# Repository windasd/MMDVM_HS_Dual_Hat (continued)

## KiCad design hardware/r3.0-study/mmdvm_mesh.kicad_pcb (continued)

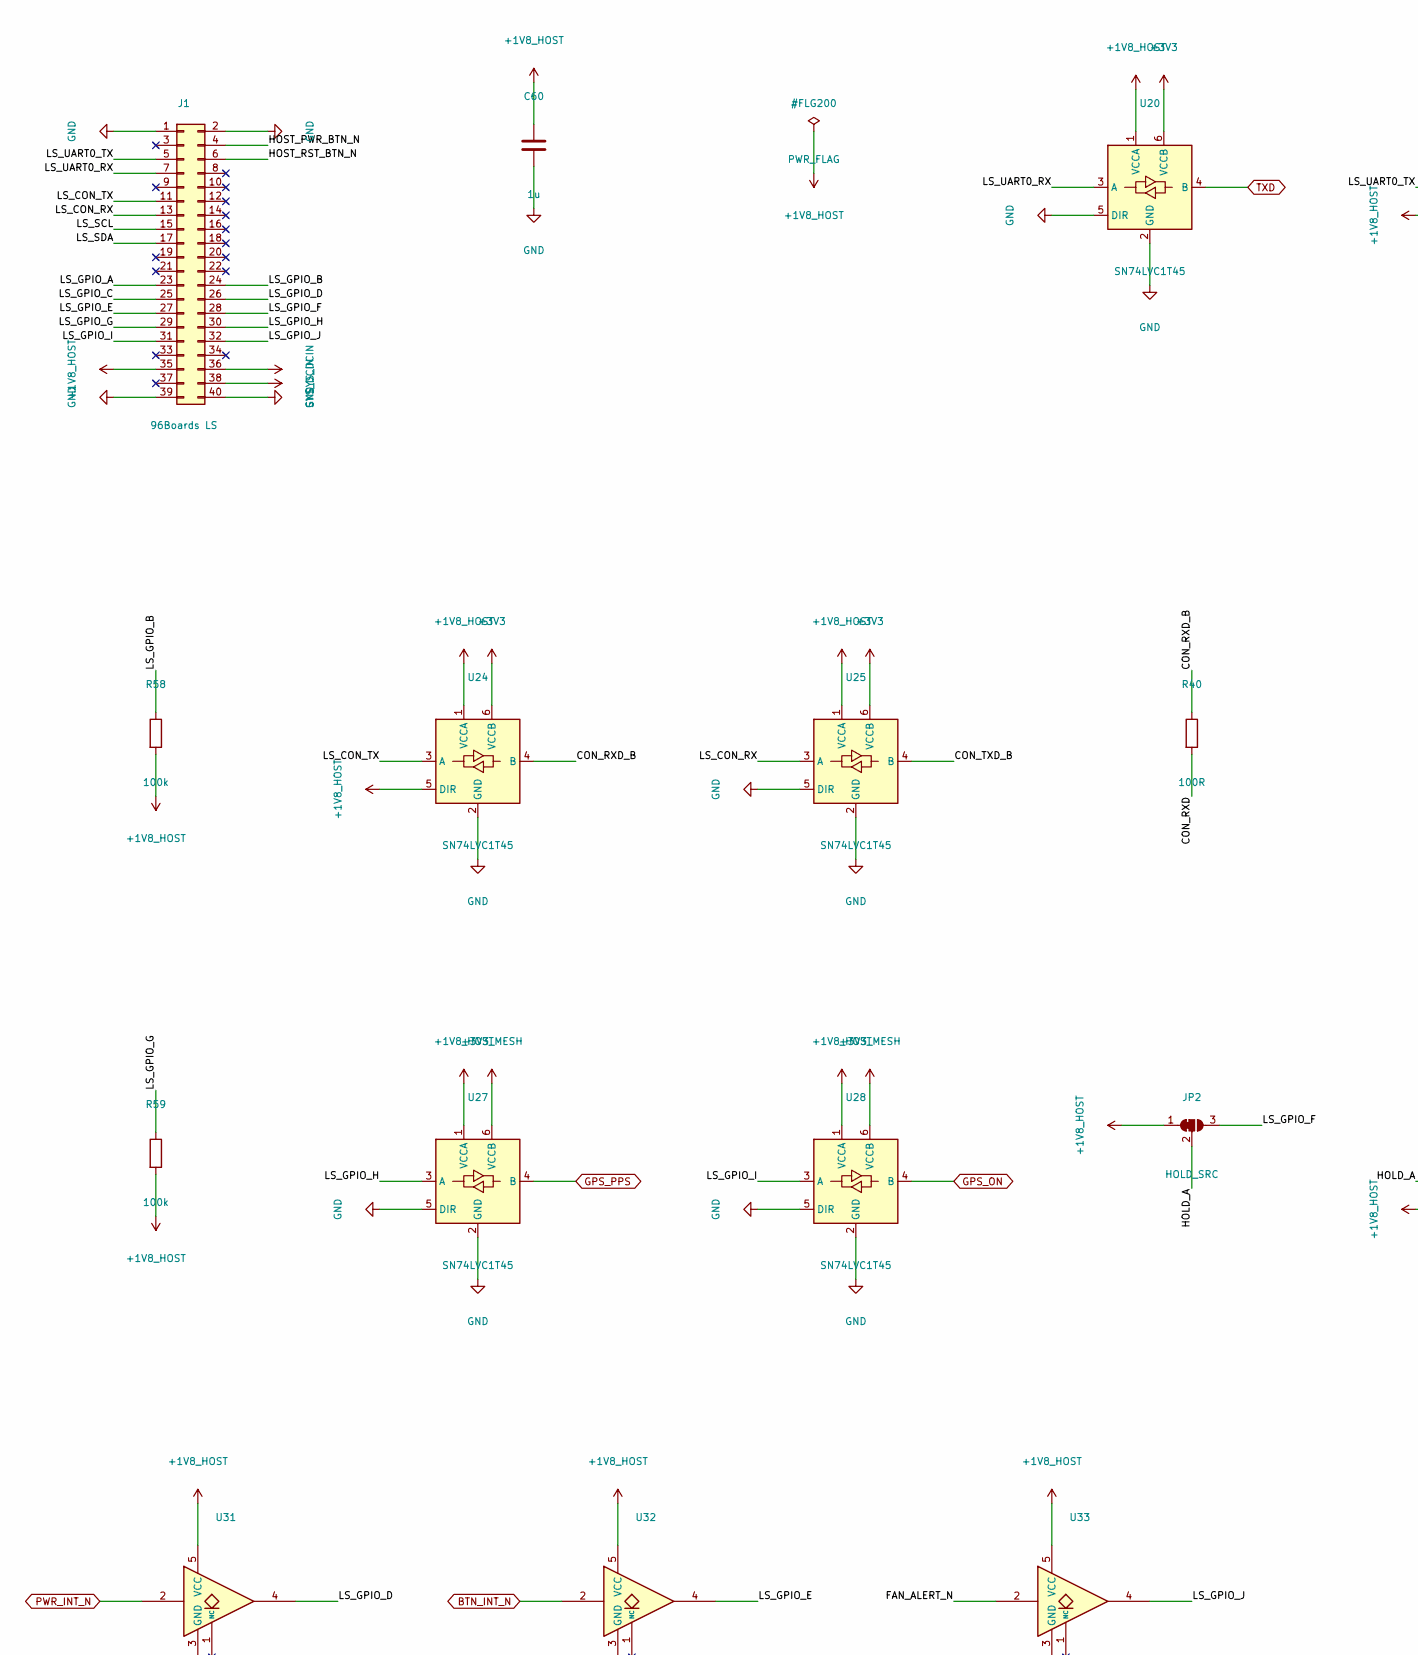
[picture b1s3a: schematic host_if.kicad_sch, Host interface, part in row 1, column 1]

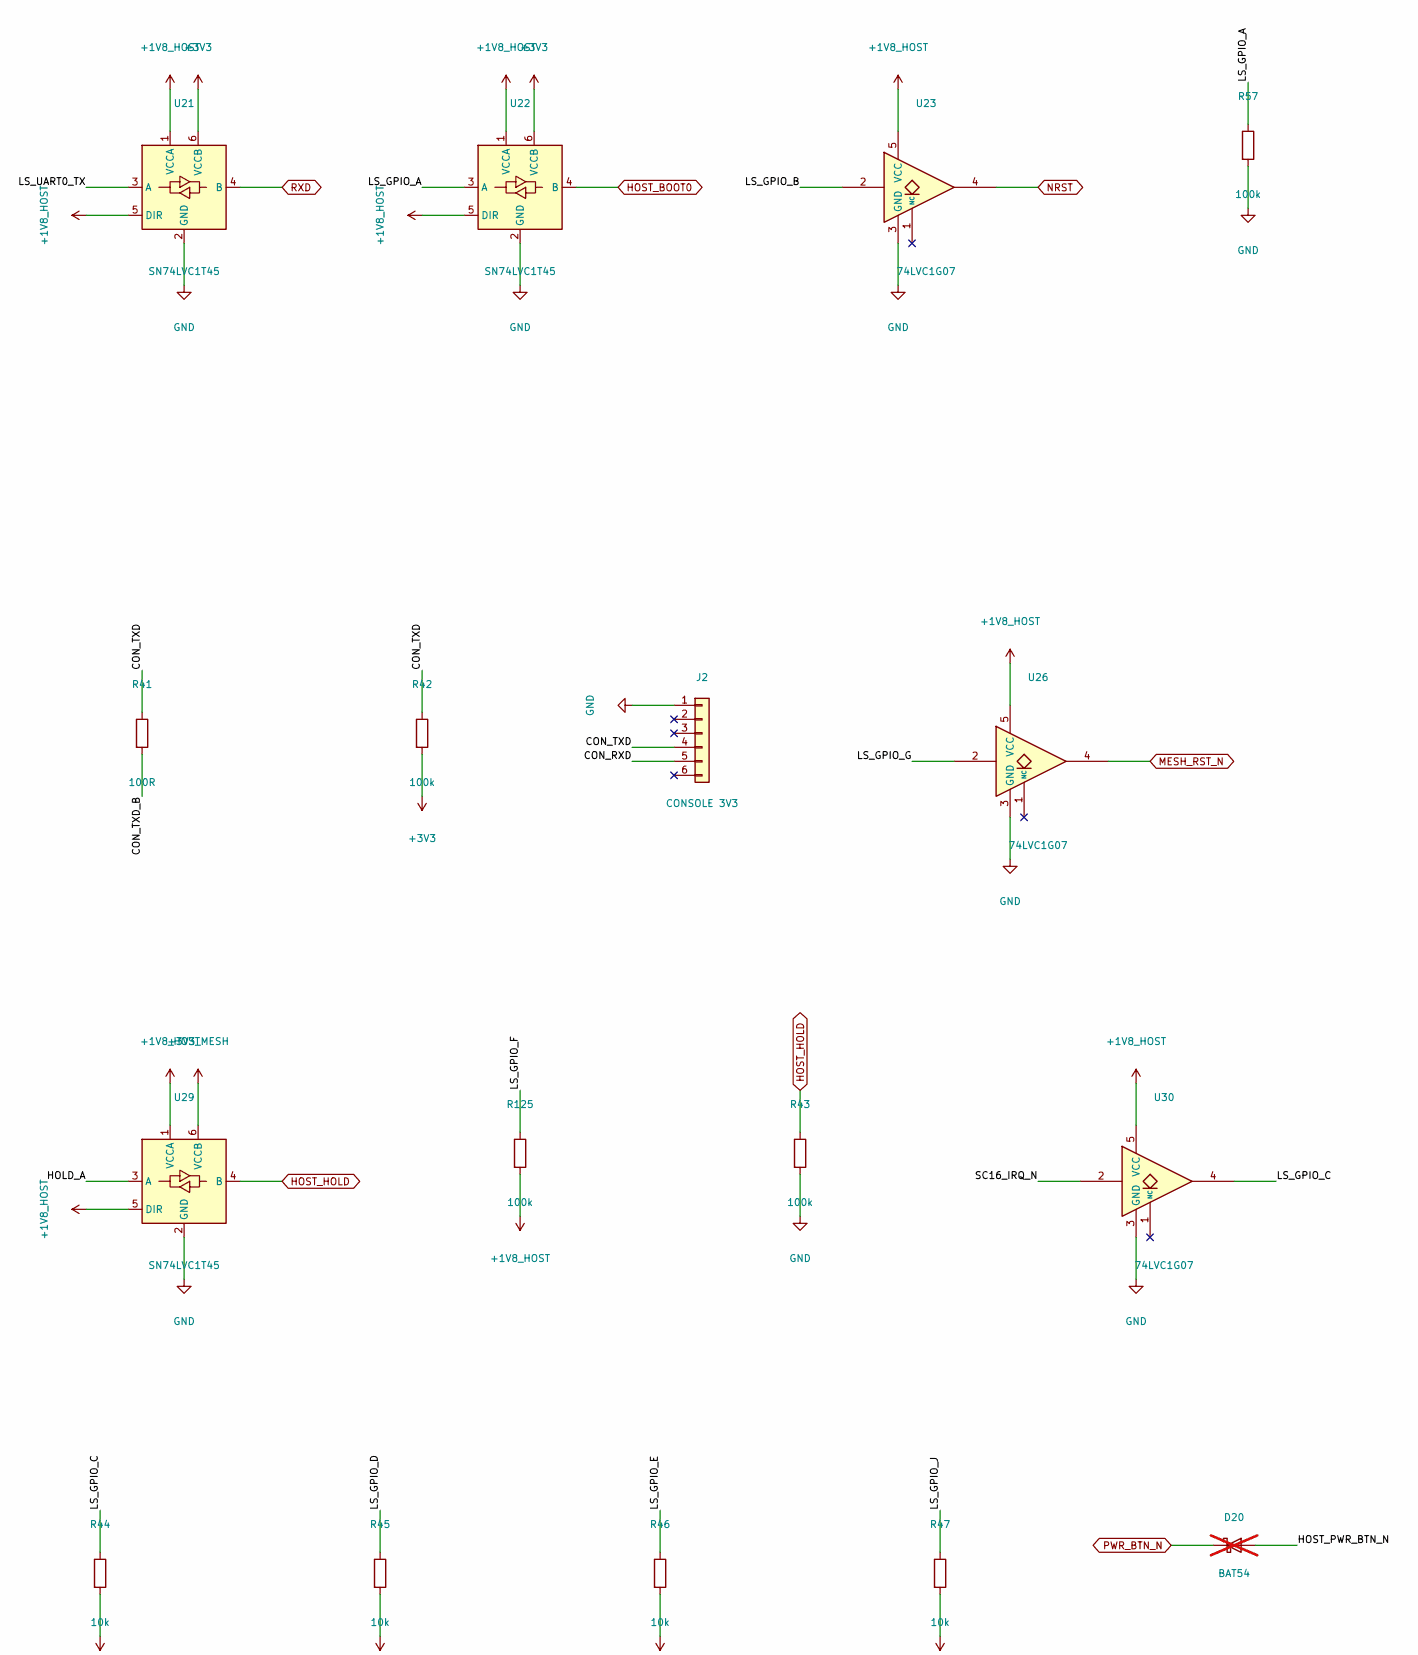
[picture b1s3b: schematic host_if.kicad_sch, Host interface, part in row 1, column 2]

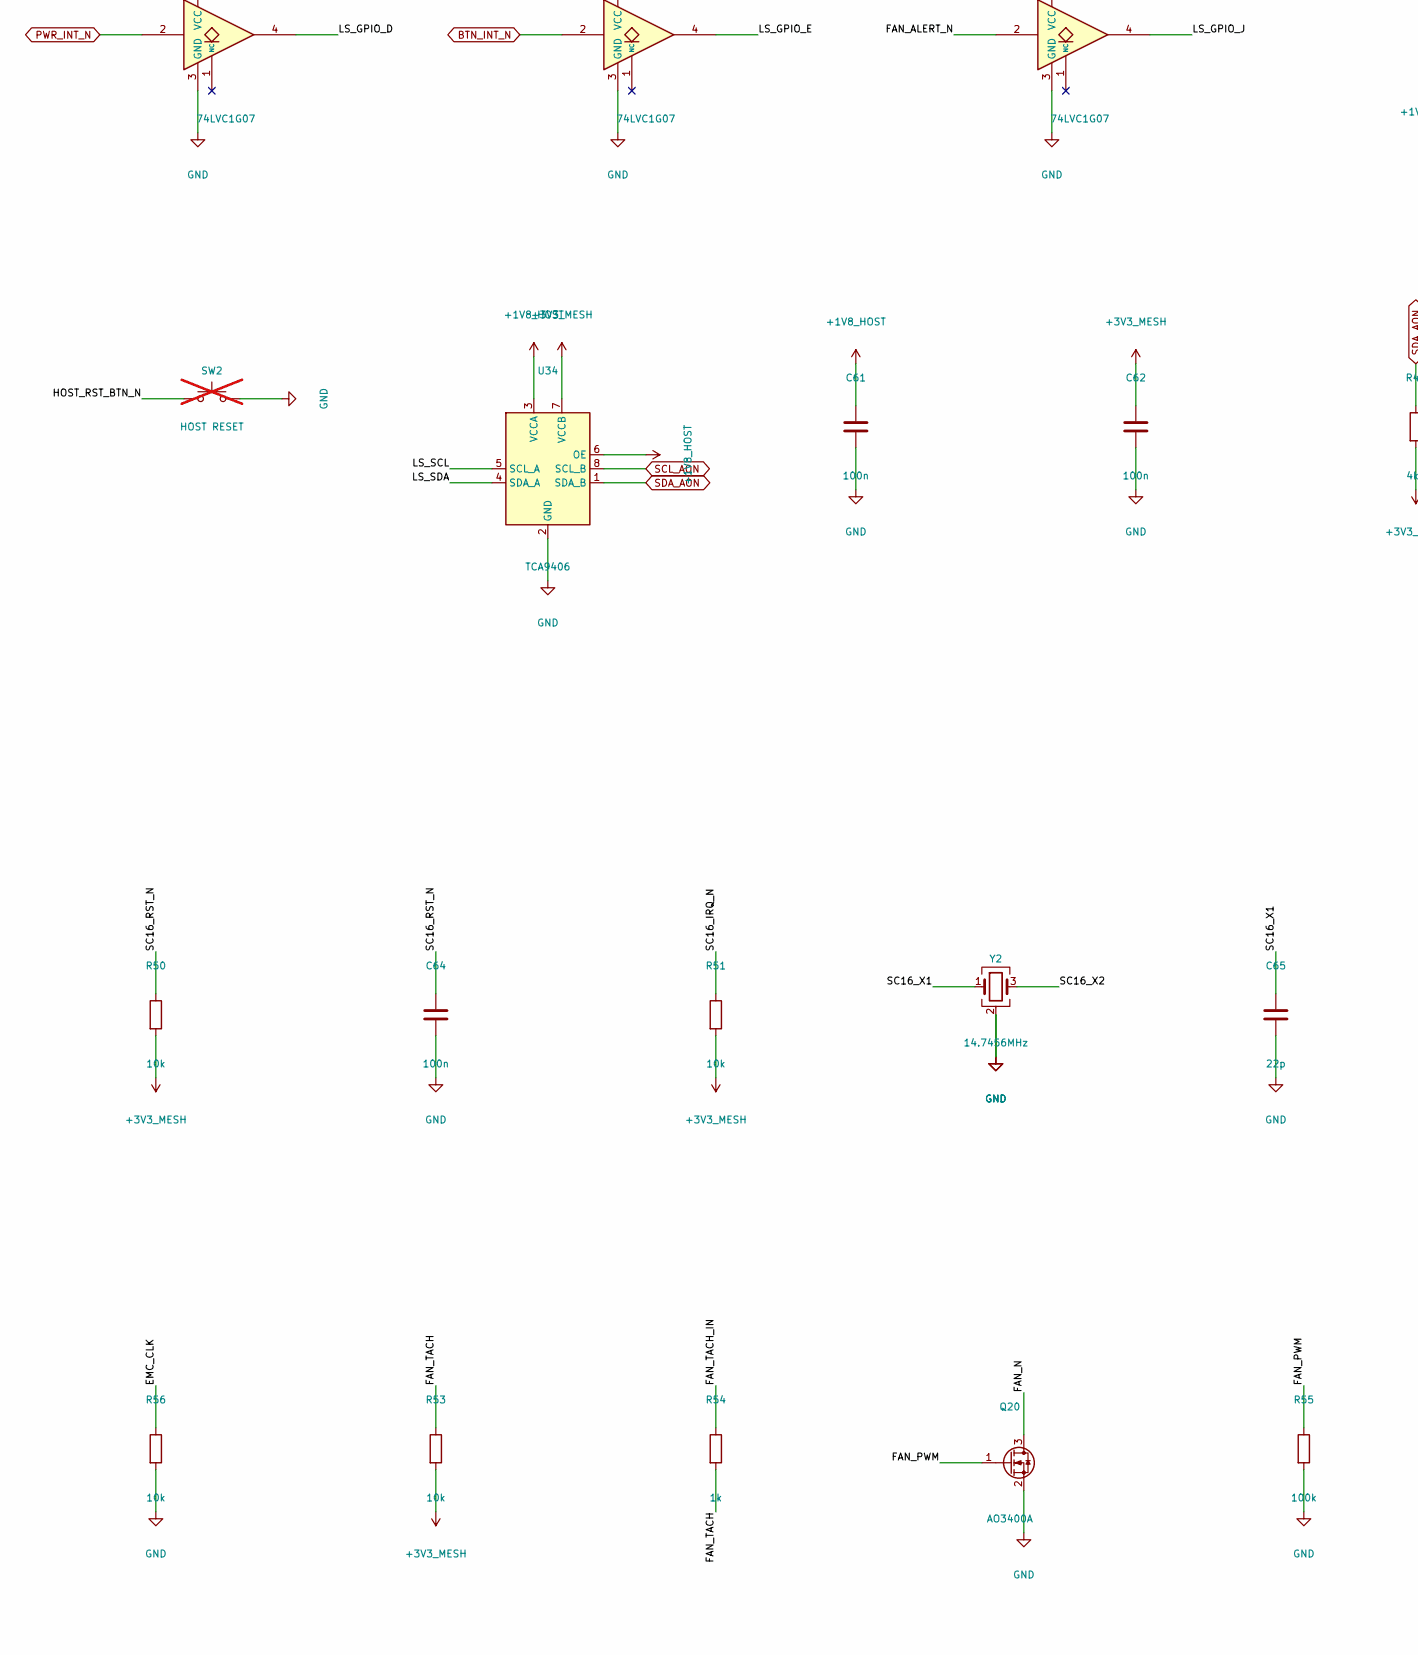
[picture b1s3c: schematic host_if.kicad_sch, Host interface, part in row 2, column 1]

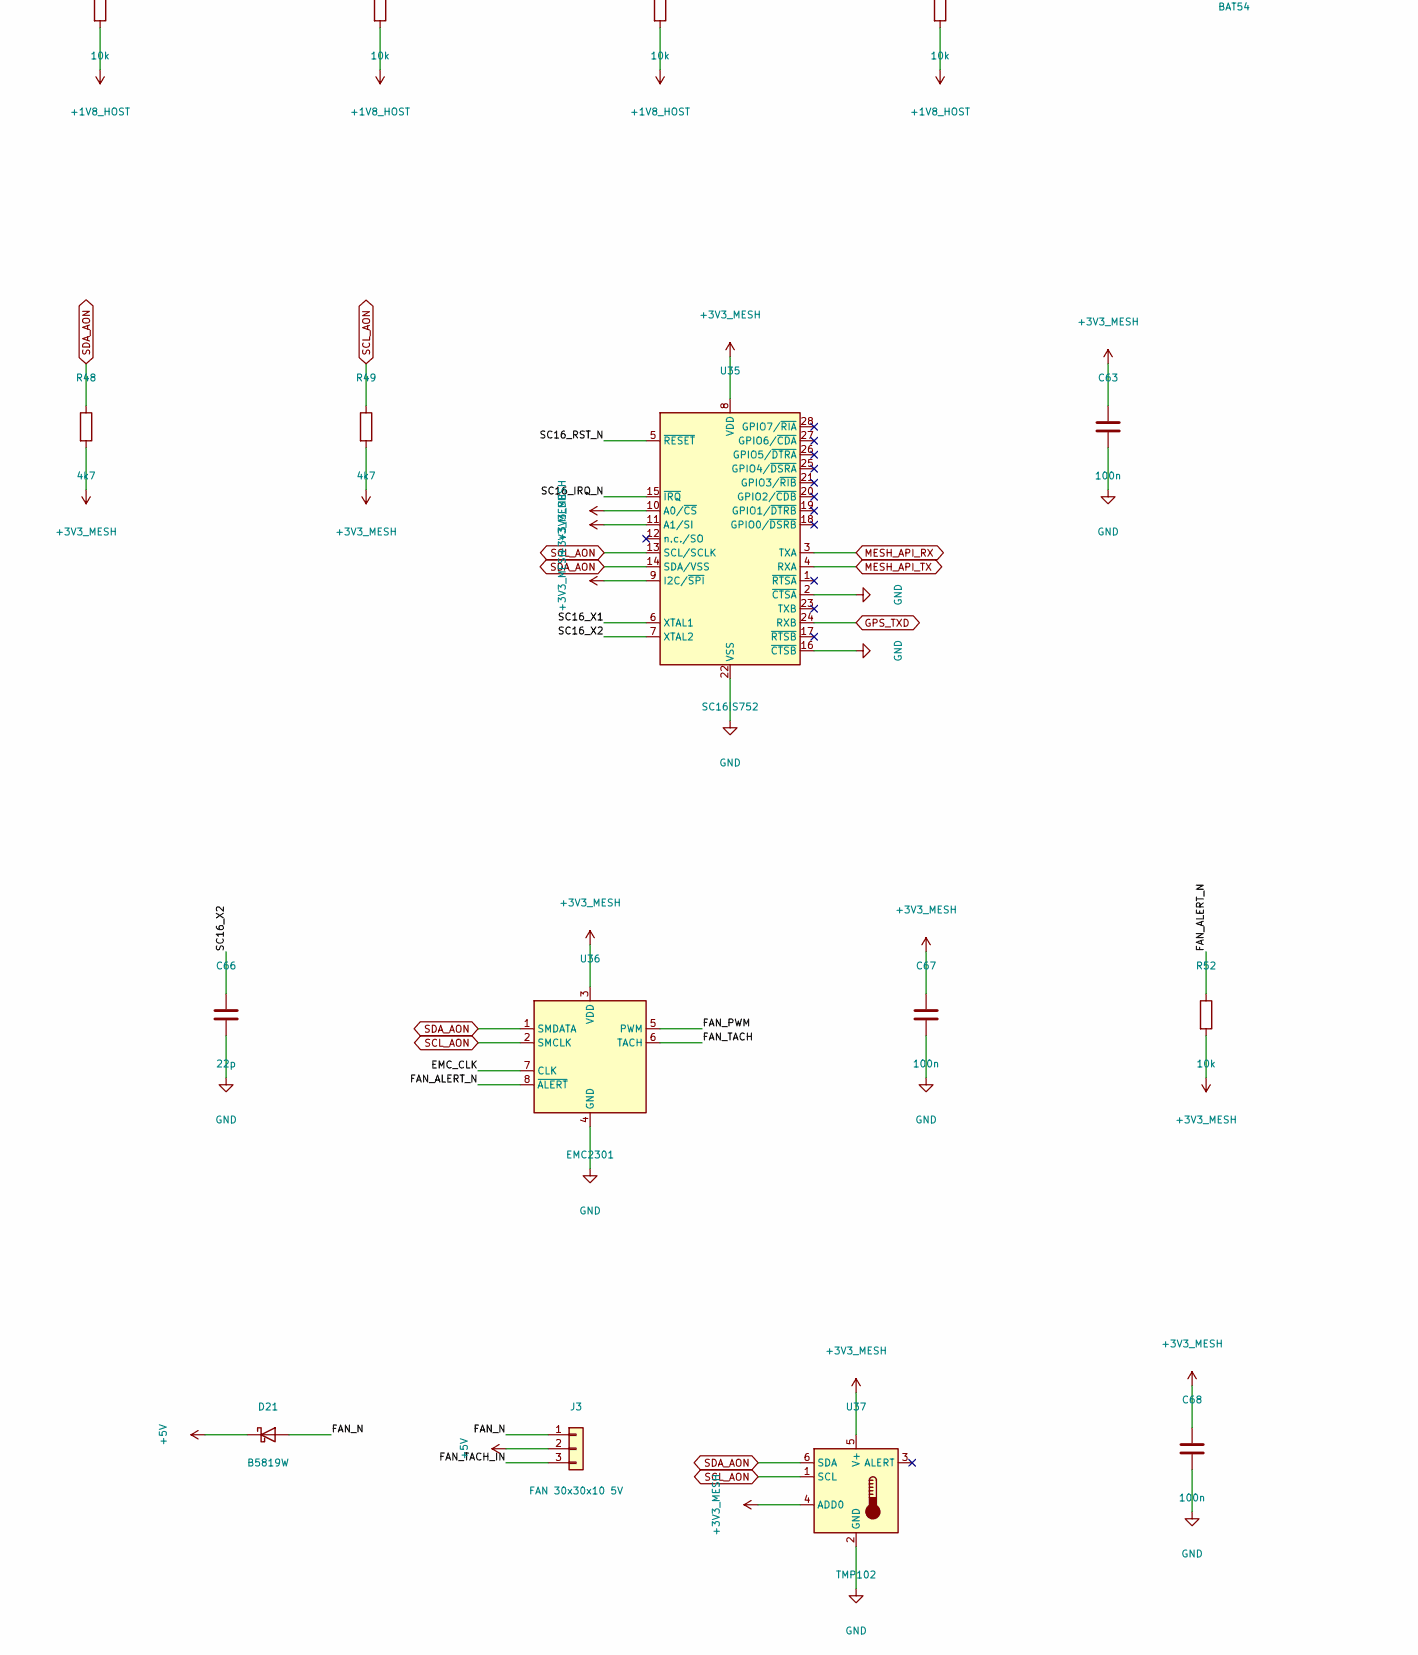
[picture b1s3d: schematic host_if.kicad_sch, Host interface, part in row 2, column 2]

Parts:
C60: 1u; C_0402_1005Metric; MPN CL05A105KA5NQNC; Mouser 187-CL05A105KA5NQNC
C61, C62, C63, C64, C67, C68: 100n; C_0402_1005Metric; MPN CL05B104KO5NNNC; Mouser 187-CL05B104KO5NNNC
C65, C66: 22p; C_0402_1005Metric; MPN 0402CG220J500NT; Mouser 187-CL05C220JB5NNNC (Mouser EQUIV: CL05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
D20: BAT54; D_SOD-323; MPN BAT54HT1G; not fitted
D21: B5819W; D_SOD-123; MPN B5819W-TP; Mouser 833-B5819W-TP
J1: 96Boards LS; LS_2x20_P2.00mm_SMD_MezzanineBottom; MPN 57202-G52-20LF; Mouser 649-57202-G52-20LF
J2: CONSOLE 3V3; PinHeader_1x06_P2.54mm_Horizontal_EdgeMount; MPN 61300611021; Mouser 710-61300611021
J3: FAN 30x30x10 5V; JST_PH_S3B-PH-SM4-TB_1x03-1MP_P2.00mm_Horizontal; MPN S3B-PH-SM4-TB(LF)(SN); Mouser 306-S3BPHSM4TBLFSN
JP2: HOLD_SRC; SolderJumper-3_P1.3mm_Bridged12_RoundedPad1.0x1.5mm
Q20: AO3400A; SOT-23; MPN AO3400A; LCSC C20917
R40, R41: 100R; R_0402_1005Metric; MPN 0402WGF1000TCE; Mouser 603-RC0402FR-07100RL
R42, R43, R55, R57, R58, R59, R125: 100k; R_0402_1005Metric; MPN 0402WGF1003TCE; Mouser 603-RC0402FR-07100KL
R44, R45, R46, R47, R50, R51, R52, R53, R56: 10k; R_0402_1005Metric; MPN 0402WGF1002TCE; Mouser 603-RC0402FR-0710KL
R48, R49: 4k7; R_0402_1005Metric; MPN 0402WGF4701TCE; Mouser 603-RC0402FR-074K7L
R54: 1k; R_0402_1005Metric; MPN 0402WGF1001TCE; Mouser 603-RC0402FR-071KL
SW2: HOST RESET; SW_SPST_B3U-1000P; MPN B3U-1000P; not fitted
U20, U21, U22, U24, U25, U27, U28, U29: SN74LVC1T45; SOT-23-6; MPN SN74LVC1T45DBVR; Mouser 595-SN74LVC1T45DBVR
U23, U26, U30, U31, U32, U33: 74LVC1G07; SOT-353_SC-70-5; MPN SN74LVC1G07DCKR; Mouser 595-SN74LVC1G07DCKR
U34: TCA9406; VSSOP-8_2.3x2mm_P0.5mm; MPN TCA9406DCUR; Mouser 595-TCA9406DCUR
U35: SC16IS752; TSSOP-28_4.4x9.7mm_P0.65mm; MPN SC16IS752IPW,128; Mouser 771-SC16IS752IPW128
U36: EMC2301; MSOP-8_3x3mm_P0.65mm; MPN EMC2301-1-ACZL-TR; Mouser 886-EMC2301-1-ACZLTR
U37: TMP102; SOT-563; MPN TMP102AIDRLR; Mouser 595-TMP102AIDRLR
Y2: 14.7456MHz; Crystal_SMD_3225-4Pin_3.2x2.5mm; MPN 7U14745AE20UCG; Mouser 815-M8147456MHZD1XT

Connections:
+1V8_HOST: C60.1, C61.1, J1.35, JP2.1 (A), R44.2, R45.2, R46.2, R47.2, R58.2, R59.2, R125.2, U20.1 (VCCA), U21.1 (VCCA), U21.5 (DIR), U22.1 (VCCA), U22.5 (DIR), U23.5 (VCC), U24.1 (VCCA), U24.5 (DIR), U25.1 (VCCA), U26.5 (VCC), U27.1 (VCCA), U28.1 (VCCA), U29.1 (VCCA), U29.5 (DIR), U30.5 (VCC), U31.5 (VCC), U32.5 (VCC), U33.5 (VCC), U34.3 (VCCA), U34.6 (OE); also elsewhere on the board
+3V3: R42.2, U20.6 (VCCB), U21.6 (VCCB), U22.6 (VCCB), U24.6 (VCCB), U25.6 (VCCB); also elsewhere on the board
+3V3_MESH: C62.1, C63.1, C67.1, C68.1, R48.2, R49.2, R50.2, R51.2, R52.2, R53.2, U27.6 (VCCB), U28.6 (VCCB), U29.6 (VCCB), U34.7 (VCCB), U35.8 (VDD), U35.9 (I2C/~SPI), U35.10 (A0/~CS), U35.11 (A1/SI), U36.3 (VDD), U37.4 (ADD0), U37.5 (V+); also elsewhere on the board
+5V: D21.1 (K), J3.2; also elsewhere on the board
/Host interface/CON_RXD: J2.5, R40.2
/Host interface/CON_RXD_B: R40.1, U24.4 (B)
/Host interface/CON_TXD: J2.4, R41.1, R42.1
/Host interface/CON_TXD_B: R41.2, U25.4 (B)
/Host interface/EMC_CLK: R56.1, U36.7 (CLK)
/Host interface/FAN_ALERT_N: R52.1, U33.2, U36.8 (~ALERT)
/Host interface/FAN_N: D21.2 (A), J3.1, Q20.3 (D)
/Host interface/FAN_PWM: Q20.1 (G), R55.1, U36.5 (PWM)
/Host interface/FAN_TACH: R53.1, R54.2, U36.6 (TACH)
/Host interface/FAN_TACH_IN: J3.3, R54.1
/Host interface/HOLD_A: JP2.2 (C), U29.3 (A)
/Host interface/HOST_PWR_BTN_N: D20.2 (A), J1.4
/Host interface/HOST_RST_BTN_N: J1.6, SW2.1
/Host interface/LS_CON_RX: J1.13, U25.3 (A)
/Host interface/LS_CON_TX: J1.11, U24.3 (A)
/Host interface/LS_GPIO_A: J1.23, R57.1, U22.3 (A)
/Host interface/LS_GPIO_B: J1.24, R58.1, U23.2
/Host interface/LS_GPIO_C: J1.25, R44.1, U30.4
/Host interface/LS_GPIO_D: J1.26, R45.1, U31.4
/Host interface/LS_GPIO_E: J1.27, R46.1, U32.4
/Host interface/LS_GPIO_F: J1.28, JP2.3 (B), R125.1
/Host interface/LS_GPIO_G: J1.29, R59.1, U26.2
/Host interface/LS_GPIO_H: J1.30, U27.3 (A)
/Host interface/LS_GPIO_I: J1.31, U28.3 (A)
/Host interface/LS_GPIO_J: J1.32, R47.1, U33.4
/Host interface/LS_SCL: J1.15, U34.5 (SCL_A)
/Host interface/LS_SDA: J1.17, U34.4 (SDA_A)
/Host interface/LS_UART0_RX: J1.7, U20.3 (A)
/Host interface/LS_UART0_TX: J1.5, U21.3 (A)
/Host interface/SC16_IRQ_N: R51.1, U30.2, U35.15 (~IRQ)
/Host interface/SC16_RST_N: C64.1, R50.1, U35.5 (~RESET)
/Host interface/SC16_X1: C65.1, U35.6 (XTAL1), Y2.1
/Host interface/SC16_X2: C66.1, U35.7 (XTAL2), Y2.3
BTN_INT_N: U32.2; also elsewhere on the board
GND: C60.2, C61.2, C62.2, C63.2, C64.2, C65.2, C66.2, C67.2, C68.2, J1.1, J1.2, J1.39, J1.40, J2.1, Q20.2 (S), R43.2, R55.2, R56.2, R57.2, SW2.2, U20.2 (GND), U20.5 (DIR), U21.2 (GND), U22.2 (GND), U23.3 (GND), U24.2 (GND), U25.2 (GND), U25.5 (DIR), U26.3 (GND), U27.2 (GND), U27.5 (DIR), U28.2 (GND), U28.5 (DIR), U29.2 (GND), U30.3 (GND), U31.3 (GND), U32.3 (GND), U33.3 (GND), U34.2 (GND), U35.2 (~CTSA), U35.16 (~CTSB), U35.22 (VSS), U36.4 (GND), U37.2 (GND), Y2.2 (G), Y2.4 (G); also elsewhere on the board
GPS_ON: U28.4 (B); also elsewhere on the board
GPS_PPS: U27.4 (B); also elsewhere on the board
GPS_TXD: U35.24 (RXB); also elsewhere on the board
HOST_BOOT0: U22.4 (B); also elsewhere on the board
HOST_HOLD: R43.1, U29.4 (B); also elsewhere on the board
MESH_API_RX: U35.3 (TXA); also elsewhere on the board
MESH_API_TX: U35.4 (RXA); also elsewhere on the board
MESH_RST_N: U26.4; also elsewhere on the board
NRST: U23.4; also elsewhere on the board
PWR_BTN_N: D20.1 (K); also elsewhere on the board
PWR_INT_N: U31.2; also elsewhere on the board
RXD: U21.4 (B); also elsewhere on the board
SCL_AON: R49.1, U34.8 (SCL_B), U35.13 (SCL/SCLK), U36.2 (SMCLK), U37.1 (SCL); also elsewhere on the board
SDA_AON: R48.1, U34.1 (SDA_B), U35.14 (SDA/VSS), U36.1 (SMDATA), U37.6 (SDA); also elsewhere on the board
SYS_DCIN: J1.36, J1.38; also elsewhere on the board
TXD: U20.4 (B); also elsewhere on the board

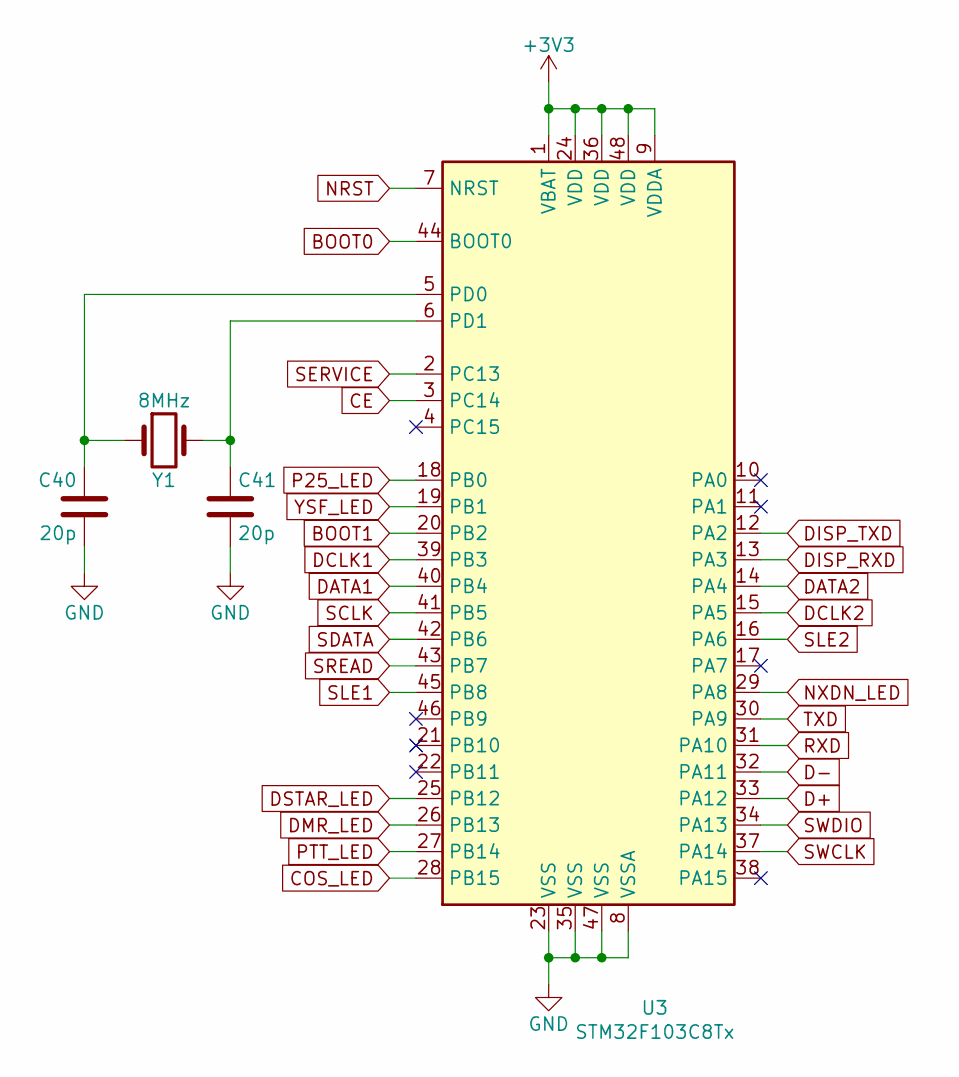
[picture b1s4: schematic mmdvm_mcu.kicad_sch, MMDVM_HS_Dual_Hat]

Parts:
C40, C41: 20p; C_0402_1005Metric; MPN GJM1555C1H200FB01D; Mouser 81-GJM1555C1H200FB1D
U3: STM32F103C8Tx; LQFP-48_7x7mm_Pitch0.5mm; MPN STM32F103C8T6; Mouser 511-STM32F103C8T6
Y1: 8MHz; Crystal_SMD_Abracon_ABM3-2Pin_5.0x3.2mm; MPN ABM3-8.000MHZ-D2Y-T; Mouser 815-ABM3-8-D2Y-T

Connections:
+3V3: U3.1 (VBAT), U3.9 (VDDA), U3.24 (VDD), U3.36 (VDD), U3.48 (VDD); also elsewhere on the board
BOOT0: U3.44 (BOOT0); also elsewhere on the board
BOOT1: U3.20 (PB2); also elsewhere on the board
CE: U3.3 (PC14); also elsewhere on the board
COS_LED: U3.28 (PB15); also elsewhere on the board
D+: U3.33 (PA12); also elsewhere on the board
D-: U3.32 (PA11); also elsewhere on the board
DATA1: U3.40 (PB4); also elsewhere on the board
DATA2: U3.14 (PA4); also elsewhere on the board
DCLK1: U3.39 (PB3); also elsewhere on the board
DCLK2: U3.15 (PA5); also elsewhere on the board
DISP_RXD: U3.13 (PA3); also elsewhere on the board
DISP_TXD: U3.12 (PA2); also elsewhere on the board
DMR_LED: U3.26 (PB13); also elsewhere on the board
DSTAR_LED: U3.25 (PB12); also elsewhere on the board
GND: C40.2, C41.2, U3.8 (VSSA), U3.23 (VSS), U3.35 (VSS), U3.47 (VSS); also elsewhere on the board
NRST: U3.7 (NRST); also elsewhere on the board
NXDN_LED: U3.29 (PA8); also elsewhere on the board
unnamed: C40.1, U3.5 (PD0), Y1.1
unnamed: C41.1, U3.6 (PD1), Y1.2
P25_LED: U3.18 (PB0); also elsewhere on the board
PTT_LED: U3.27 (PB14); also elsewhere on the board
RXD: U3.31 (PA10); also elsewhere on the board
SCLK: U3.41 (PB5); also elsewhere on the board
SDATA: U3.42 (PB6); also elsewhere on the board
SERVICE: U3.2 (PC13); also elsewhere on the board
SLE1: U3.45 (PB8); also elsewhere on the board
SLE2: U3.16 (PA6); also elsewhere on the board
SREAD: U3.43 (PB7); also elsewhere on the board
SWCLK: U3.37 (PA14); also elsewhere on the board
SWDIO: U3.34 (PA13); also elsewhere on the board
TXD: U3.30 (PA9); also elsewhere on the board
YSF_LED: U3.19 (PB1); also elsewhere on the board

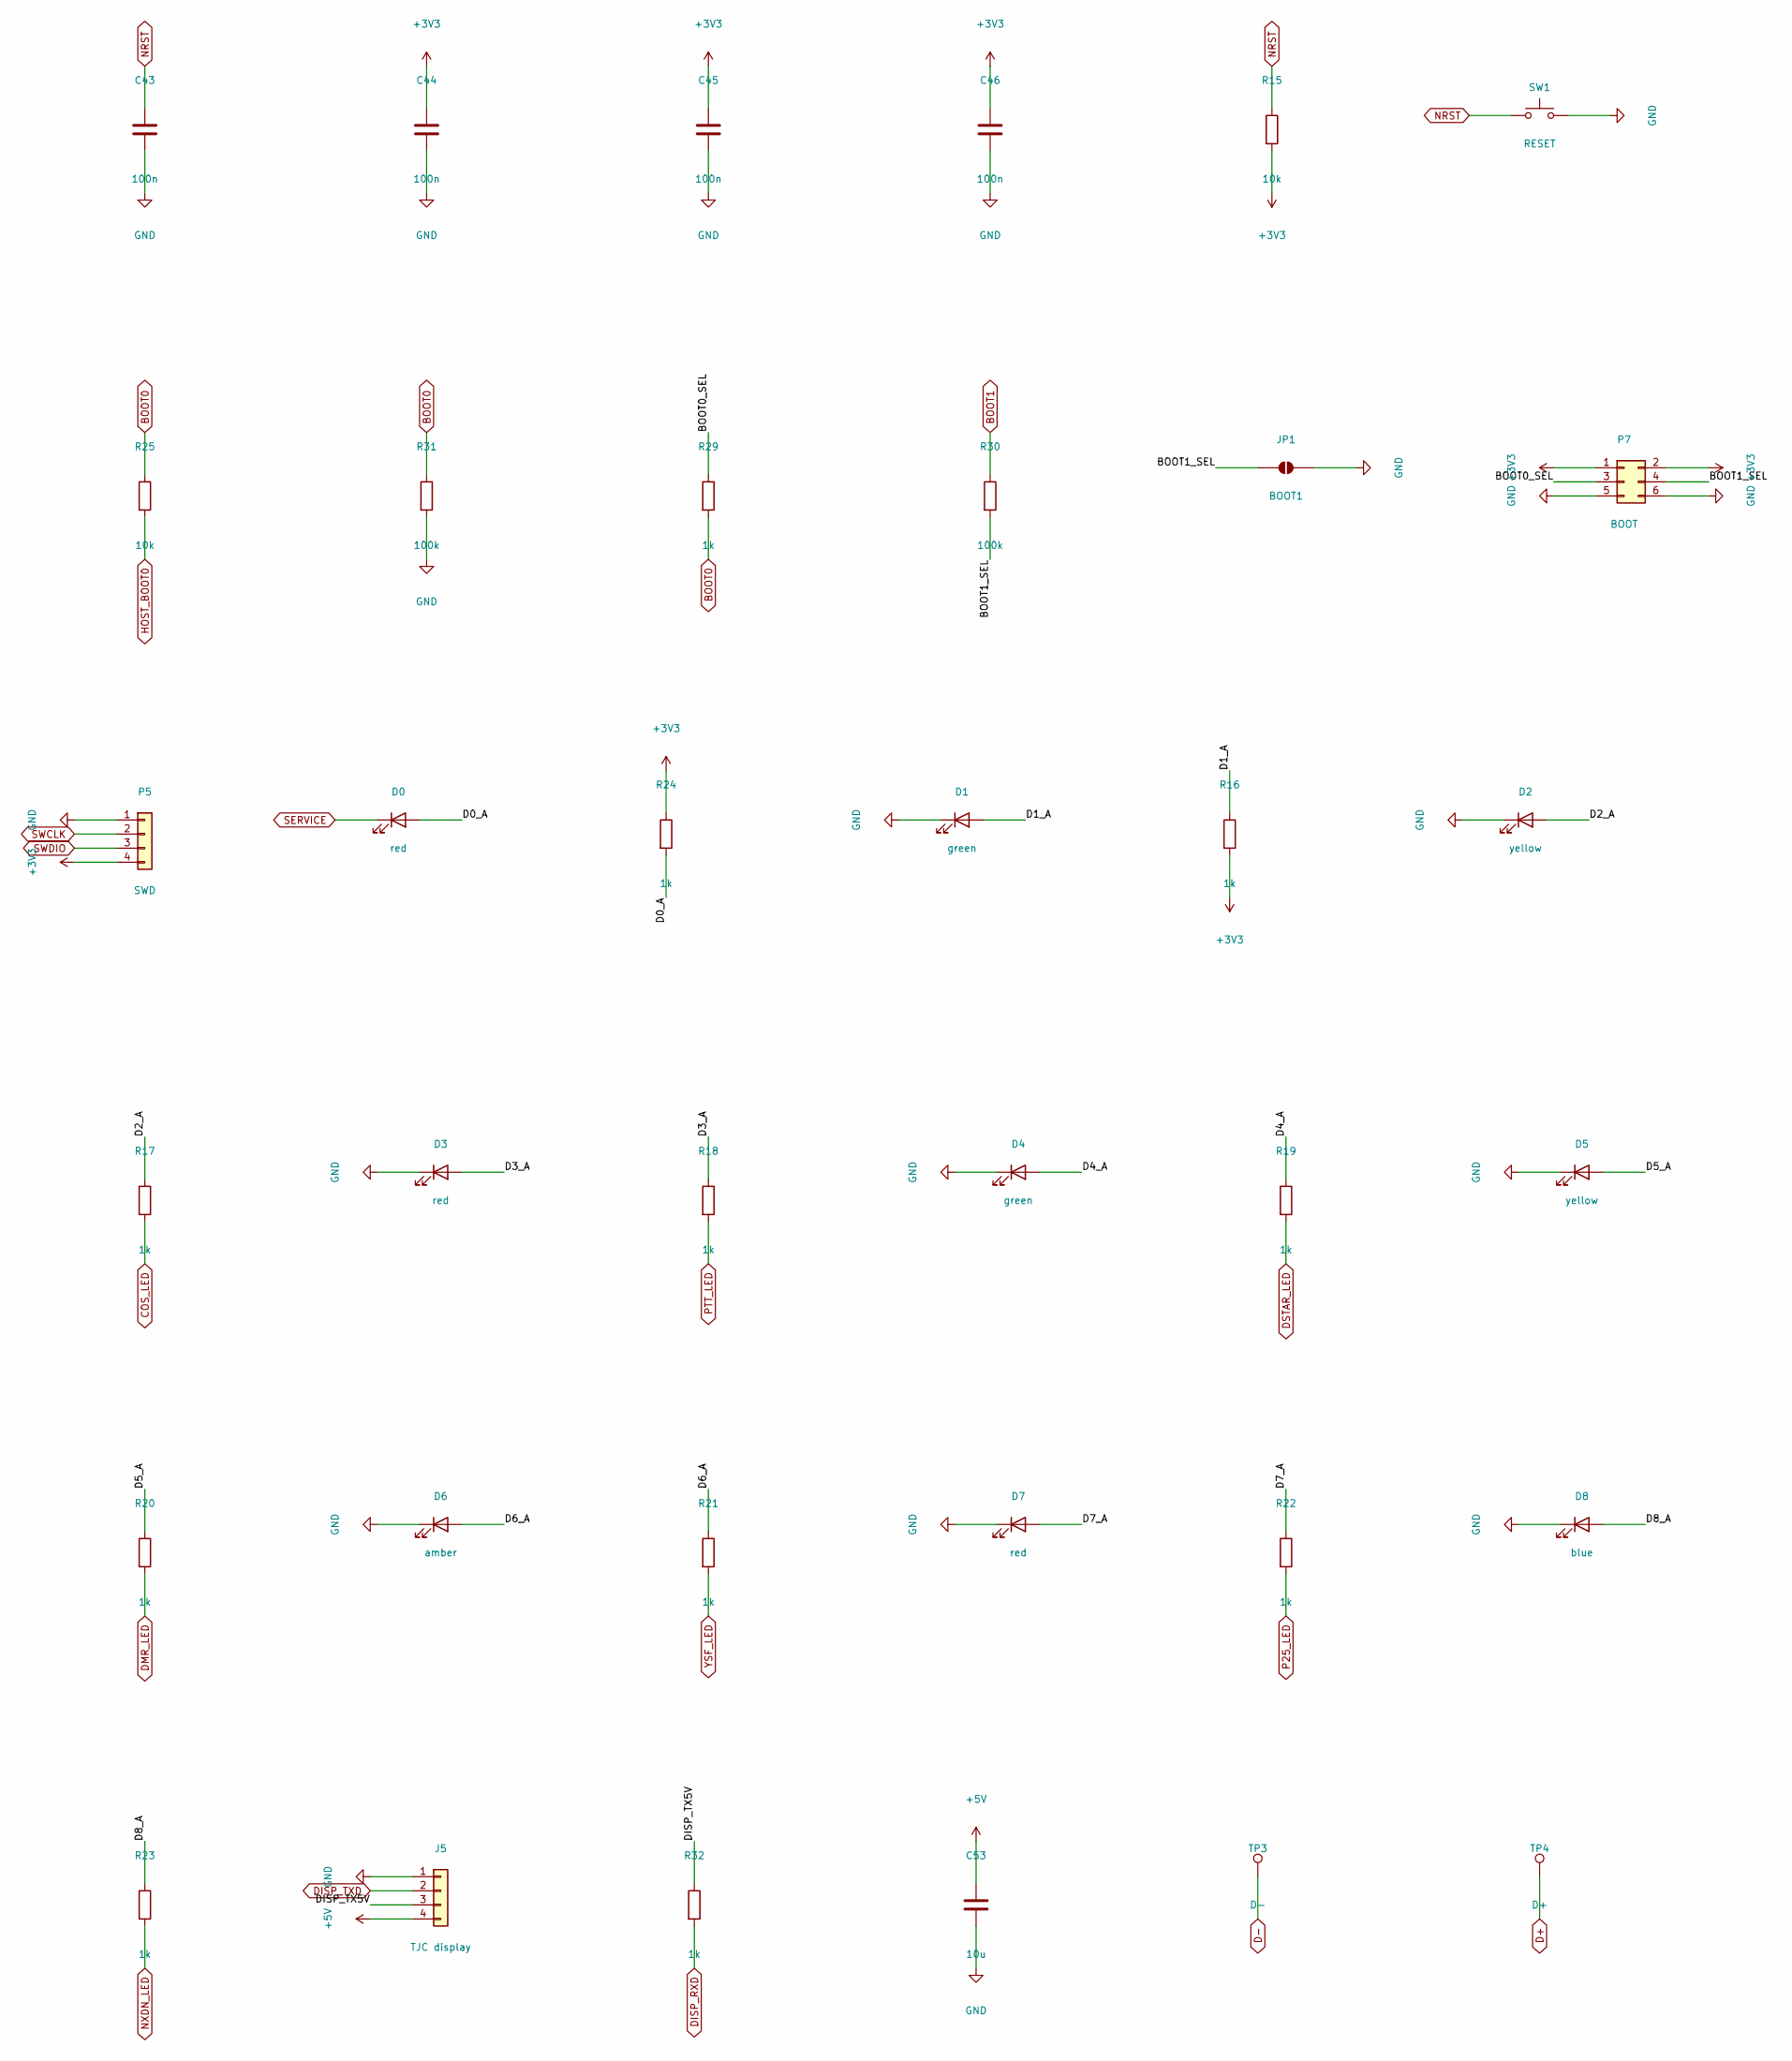
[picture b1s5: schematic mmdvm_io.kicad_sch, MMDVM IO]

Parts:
C43, C44, C45, C46: 100n; C_0402_1005Metric; MPN CL05B104KO5NNNC; Mouser 187-CL05B104KO5NNNC
C53: 10u; C_0805_2012Metric; MPN CL21A106KAYNNNE; Mouser 187-CL21A106KAYNNNE
D0, D3, D7: red; LED_0402_1005Metric; MPN APHHS1005SURCK; Mouser 604-APHHS1005SURCK
D1, D4: green; LED_0402_1005Metric; MPN APHHS1005LCGCK; Mouser 604-APHHS1005CGCK
D2, D5: yellow; LED_0402_1005Metric; MPN APHHS1005SYCK; Mouser 604-APHHS1005SYCK
D6: amber; LED_0402_1005Metric; MPN APHHS1005SECK; Mouser 604-APHHS1005SECK
D8: blue; LED_0402_1005Metric; MPN APHHS1005QBC/D; Mouser 604-APHHS1005QBCD
J5: TJC display; JST_XH_B4B-XH-A_1x04_P2.50mm_Vertical; MPN B4B-XH-A(LF)(SN); Mouser 306-B4BXHALFSN
JP1: BOOT1; SolderJumper-2_P1.3mm_Open_TrianglePad1.0x1.5mm
P5: SWD; PinHeader_1x04_P2.54mm_Vertical; MPN 61300411121; Mouser 710-61300411121
P7: BOOT; PinHeader_2x03_P2.54mm_Vertical; MPN 61300621121; Mouser 710-61300621121
R15, R25: 10k; R_0402_1005Metric; MPN 0402WGF1002TCE; Mouser 603-RC0402FR-0710KL
R16, R17, R18, R19, R20, R21, R22, R23, R24, R29, R32: 1k; R_0402_1005Metric; MPN 0402WGF1001TCE; Mouser 603-RC0402FR-071KL
R30, R31: 100k; R_0402_1005Metric; MPN 0402WGF1003TCE; Mouser 603-RC0402FR-07100KL
SW1: RESET; SW_SPST_B3U-1000P; MPN B3U-1000P; Mouser 653-B3U-1000P
TP3: D-; TestPoint_Pad_D1.0mm
TP4: D+; TestPoint_Pad_D1.0mm

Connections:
+3V3: C44.1, C45.1, C46.1, P5.4, P7.1, P7.2, R15.2, R16.2, R24.1; also elsewhere on the board
+5V: C53.1, J5.4; also elsewhere on the board
/MMDVM IO/BOOT0_SEL: P7.3, R29.1
/MMDVM IO/BOOT1_SEL: JP1.1 (A), P7.4, R30.2
/MMDVM IO/D0_A: D0.2 (A), R24.2
/MMDVM IO/D1_A: D1.2 (A), R16.1
/MMDVM IO/D2_A: D2.2 (A), R17.1
/MMDVM IO/D3_A: D3.2 (A), R18.1
/MMDVM IO/D4_A: D4.2 (A), R19.1
/MMDVM IO/D5_A: D5.2 (A), R20.1
/MMDVM IO/D6_A: D6.2 (A), R21.1
/MMDVM IO/D7_A: D7.2 (A), R22.1
/MMDVM IO/D8_A: D8.2 (A), R23.1
/MMDVM IO/DISP_TX5V: J5.3, R32.1
BOOT0: R25.1, R29.2, R31.1; also elsewhere on the board
BOOT1: R30.1; also elsewhere on the board
COS_LED: R17.2; also elsewhere on the board
D+: TP4.1; also elsewhere on the board
D-: TP3.1; also elsewhere on the board
DISP_RXD: R32.2; also elsewhere on the board
DISP_TXD: J5.2; also elsewhere on the board
DMR_LED: R20.2; also elsewhere on the board
DSTAR_LED: R19.2; also elsewhere on the board
GND: C43.2, C44.2, C45.2, C46.2, C53.2, D1.1 (K), D2.1 (K), D3.1 (K), D4.1 (K), D5.1 (K), D6.1 (K), D7.1 (K), D8.1 (K), J5.1, JP1.2 (B), P5.1, P7.5, P7.6, R31.2, SW1.2; also elsewhere on the board
HOST_BOOT0: R25.2; also elsewhere on the board
NRST: C43.1, R15.1, SW1.1; also elsewhere on the board
NXDN_LED: R23.2; also elsewhere on the board
P25_LED: R22.2; also elsewhere on the board
PTT_LED: R18.2; also elsewhere on the board
SERVICE: D0.1 (K); also elsewhere on the board
SWCLK: P5.2; also elsewhere on the board
SWDIO: P5.3; also elsewhere on the board
YSF_LED: R21.2; also elsewhere on the board
